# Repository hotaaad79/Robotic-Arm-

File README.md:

# Robotic Arm Control using STM32

## Overview

This project controls a 4-DOF robotic arm using STM32 microcontroller.

The robotic arm can be controlled using two different modes:

- Joystick Control Mode
- Potentiometer Control Mode

---

## Features

- Control 4 Servo Motors
- Dual Control Mode
- Smooth and precise movement
- Real-time control

---

## Hardware Components

- STM32 Microcontroller
- Servo Motors (4)
- Joysticks (2)
- Potentiometers
- Power Supply

---

## Software Tools

- STM32CubeIDE
- Embedded C

---

## Hardware Implementation

The circuit was fully implemented by soldering all components and wires on a perfboard (donut board) to ensure reliable and permanent connections.

---

## PCB Design

The PCB was designed using KiCad, but it was not fabricated.

---

## Control Modes

### Mode 1 – Joystick

Each joystick controls two motors.

### Mode 2 – Potentiometer

Each potentiometer controls one motor.

---
---

## Author
Mohamed Abdelnabi
Electrical Engineering Student

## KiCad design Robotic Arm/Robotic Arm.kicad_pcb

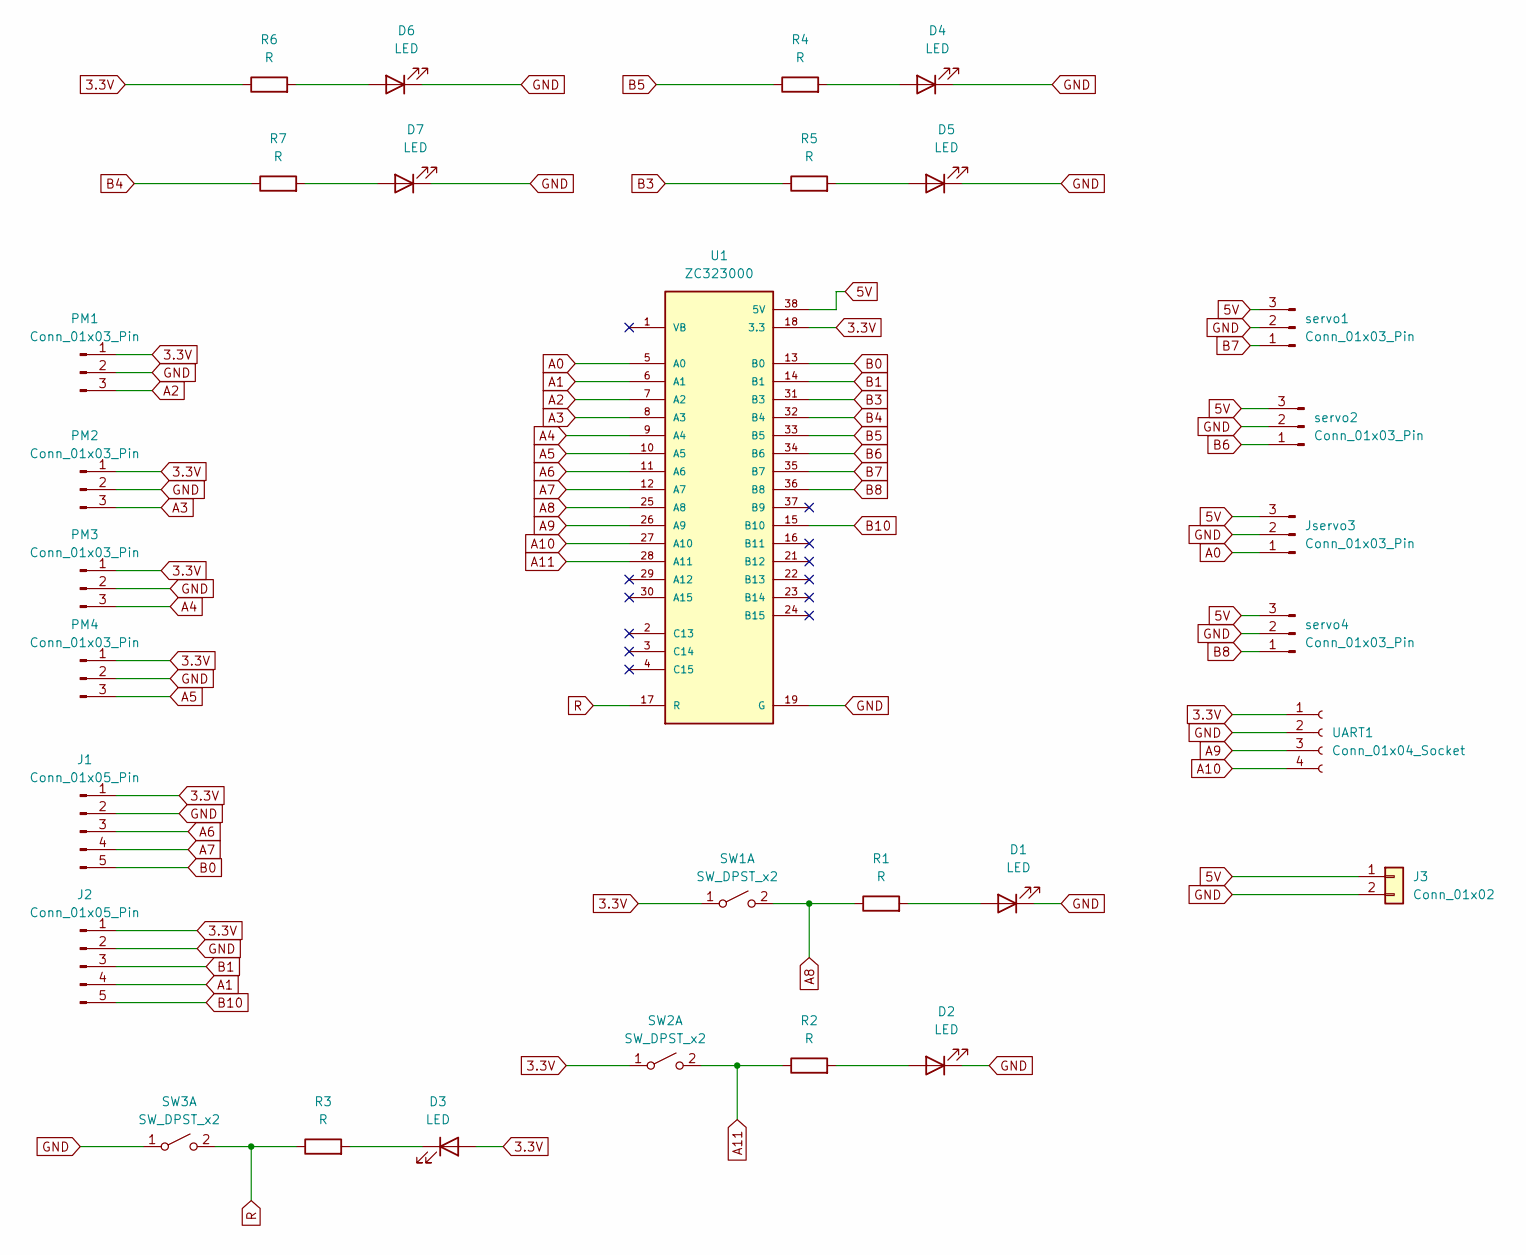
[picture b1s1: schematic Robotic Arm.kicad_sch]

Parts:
D1, D2, D3, D4, D5, D6, D7: LED; LED_D4.0mm
J1, J2: Conn_01x05_Pin; PinHeader_1x05_P2.54mm_Vertical
J3: Conn_01x02; TerminalBlock_Xinya_XY308-2.54-2P_1x02_P2.54mm_Horizontal
Jservo3: Conn_01x03_Pin; PinHeader_1x03_P2.54mm_Vertical
PM1, PM2, PM3, PM4: Conn_01x03_Pin; PinHeader_1x03_P2.54mm_Vertical
R1, R2, R3, R4, R5, R6, R7: R; R_Axial_DIN0207_L6.3mm_D2.5mm_P10.16mm_Horizontal
SW1, SW2, SW3: SW_DPST_x2; SW_PUSH_6mm_H13mm
U1: ZC323000; MODULE_ZC323000; PARTREV N/A
UART1: Conn_01x04_Socket; PinHeader_1x04_P2.54mm_Vertical
servo1, servo2, servo4: Conn_01x03_Pin; PinHeader_1x03_P2.54mm_Vertical

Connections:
3.3V: D3.2 (A), J1.1, J2.1, PM1.1, PM2.1, PM3.1, PM4.1, R6.1, SW1.1 (A), SW2.1 (A), U1.18 (3.3), U1.40 (3.3), UART1.1
5V: J3.1, Jservo3.3, U1.38 (5V), servo1.3, servo2.3, servo4.3
A0: Jservo3.1, U1.5 (A0)
A1: J2.4, U1.6 (A1)
A2: PM1.3, U1.7 (A2)
A3: PM2.3, U1.8 (A3)
A4: PM3.3, U1.9 (A4)
A5: PM4.3, U1.10 (A5)
A6: J1.3, U1.11 (A6)
A7: J1.4, U1.12 (A7)
A8: R1.1, SW1.2 (B), U1.25 (A8)
A9: U1.26 (A9), UART1.3
A10: U1.27 (A10), UART1.4
A11: R2.1, SW2.2 (B), U1.28 (A11)
B0: J1.5, U1.13 (B0)
B1: J2.3, U1.14 (B1)
B3: R5.1, U1.31 (B3)
B4: R7.1, U1.32 (B4)
B5: R4.1, U1.33 (B5)
B6: U1.34 (B6), servo2.1
B7: U1.35 (B7), servo1.1
B8: U1.36 (B8), servo4.1
B10: J2.5, U1.15 (B10)
GND: D1.1 (K), D2.1 (K), D4.1 (K), D5.1 (K), D6.1 (K), D7.1 (K), J1.2, J2.2, J3.2, Jservo3.2, PM1.2, PM2.2, PM3.2, PM4.2, SW3.1 (A), U1.19 (G), U1.20 (G), U1.39 (G), UART1.2, servo1.2, servo2.2, servo4.2
unnamed: D1.2 (A), R1.2
unnamed: D2.2 (A), R2.2
unnamed: D3.1 (K), R3.2
unnamed: D4.2 (A), R4.2
unnamed: D5.2 (A), R5.2
unnamed: D6.2 (A), R6.2
unnamed: D7.2 (A), R7.2
R: R3.1, SW3.2 (B), U1.17 (R)

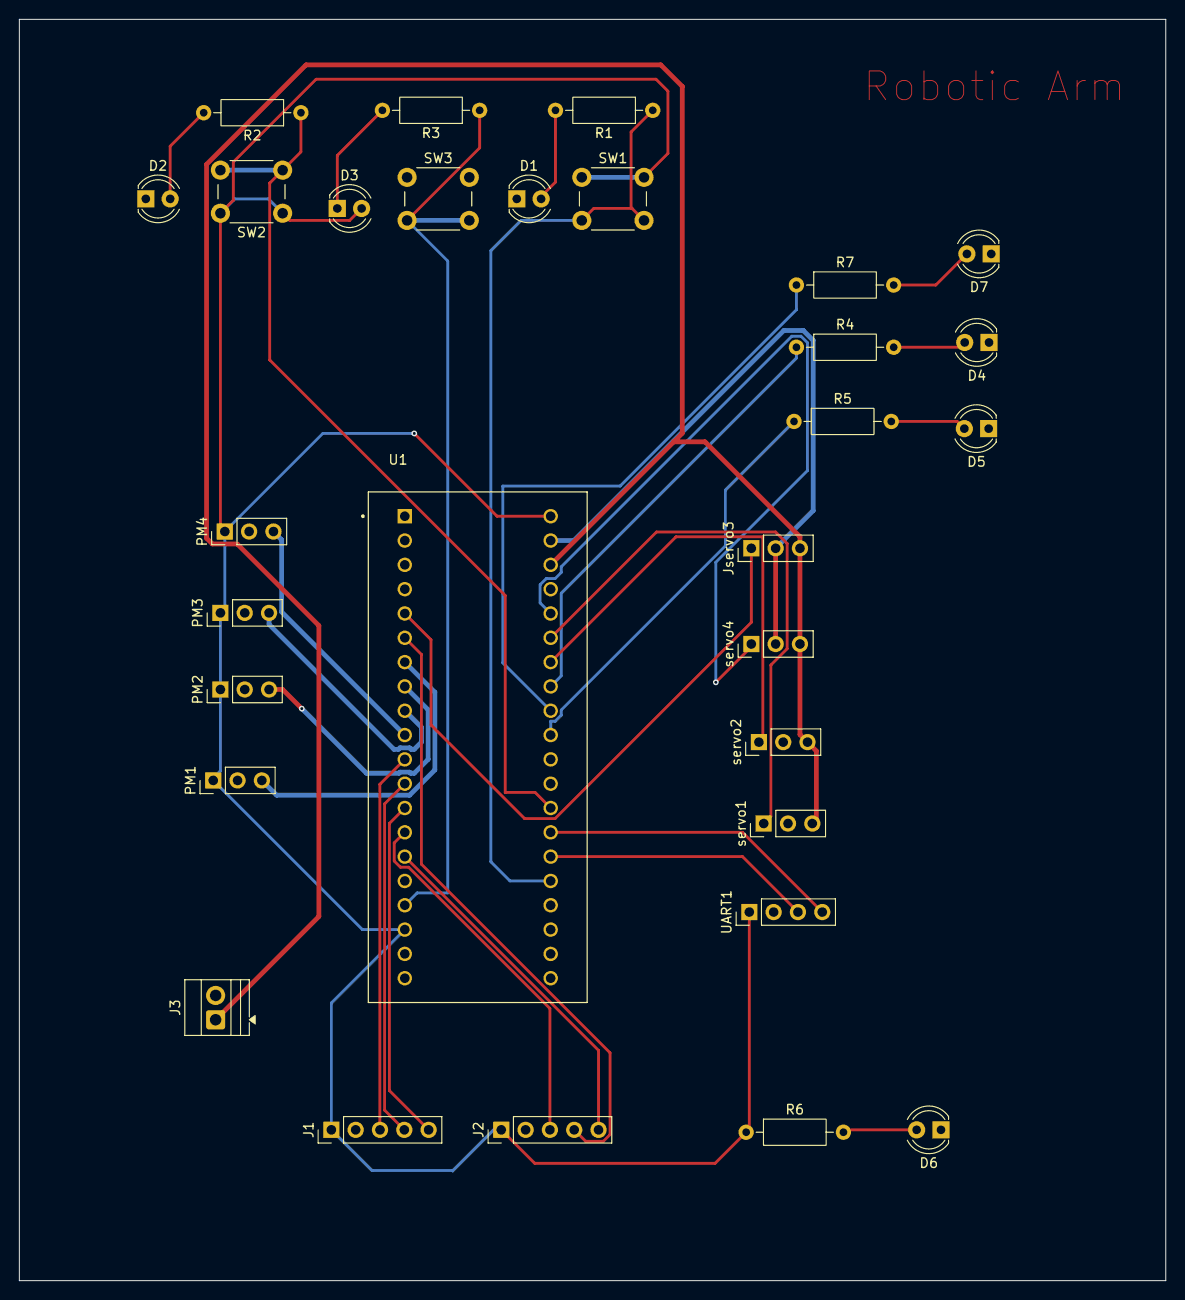
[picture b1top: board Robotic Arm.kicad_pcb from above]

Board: 2 copper layers, 119.8 x 131.8 mm, 30 parts (0 on the bottom side), 32 nets.
